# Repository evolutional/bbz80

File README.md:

# BBZ80

A breadboard Z80 computer loosely based on the Amstrad CPC 464 and targeting the RC2014 bus standard.

This is a work in progress project. Follow the story [on the blog](https://www.evolutional.co.uk/categories/bbz80/).

## Modules

- [Backplane](./docs/backplane/README.md)
- [Z80 CPU Board](./docs/z80-board/README.md)
- Clock board - TBD
- Serial IO board - TBD

## Acknowledgements

This project uses designs and standards based on [RC2014](https://rc2014.co.uk). It is not endorsed by or affiliated with RC2014 in any way whatsoever.

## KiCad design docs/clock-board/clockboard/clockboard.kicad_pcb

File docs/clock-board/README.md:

# Clock Board

The clock board takes a 16Mz oscillator and divides down to 8Mhz, 4Mhz, 2Mhz and 1Mhz clocks that can be mapped to the RC2014 `CLK` and/or `CLK2` lines.

Additionally, it has provision for an external clock `EXT` line that can be exposed to RC2014's `CLK` and/or `CLK2` lines.

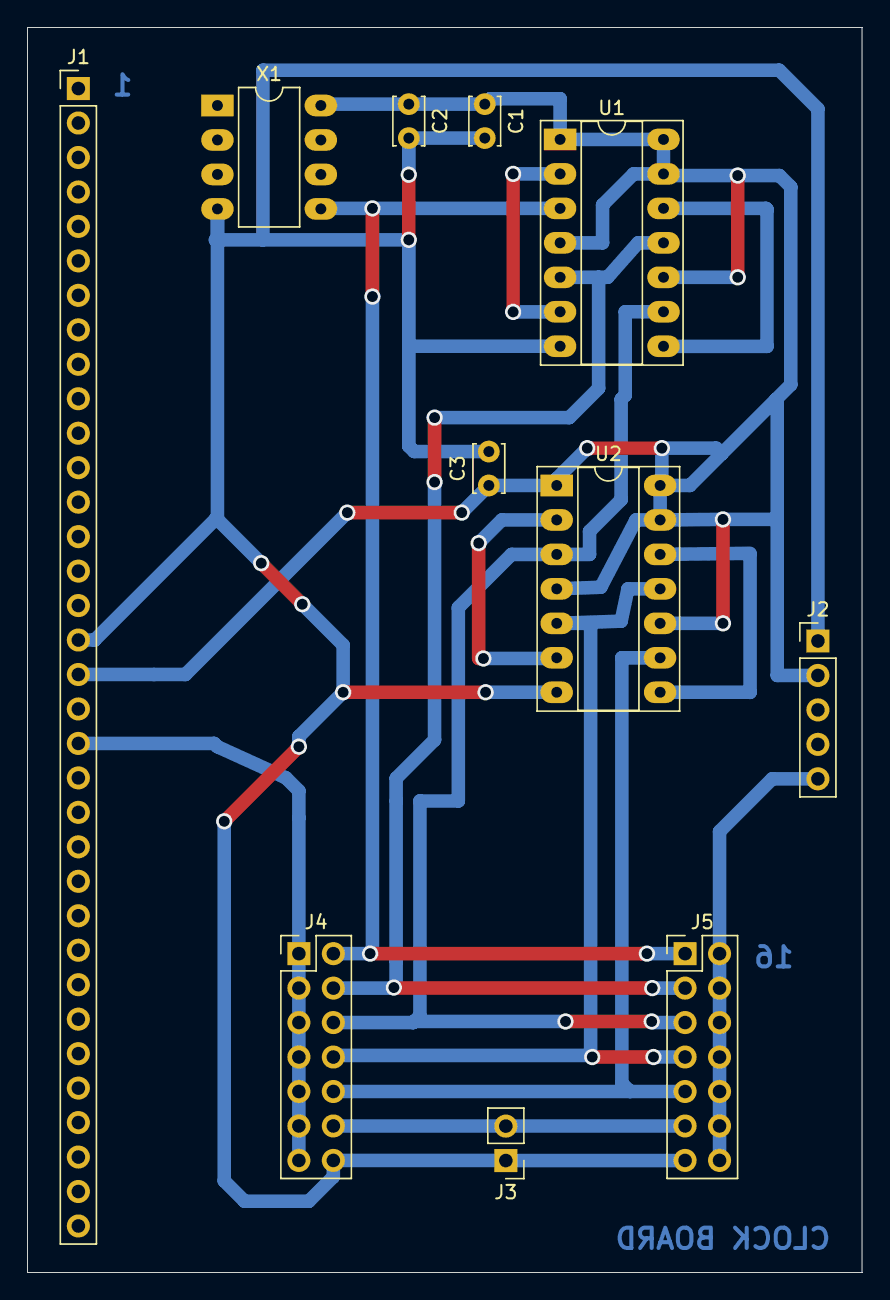
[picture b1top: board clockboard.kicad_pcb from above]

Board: 2 copper layers, 61.5 x 91.8 mm, 11 parts (0 on the bottom side), 14 nets.

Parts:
C1, C2, C3: C; C_Disc_D3.4mm_W2.1mm_P2.50mm
J1: Conn_01x34_Male; PinHeader_1x34_P2.54mm_Vertical
J2: Conn_01x05_Male; PinHeader_1x05_P2.54mm_Vertical
J3: Conn_01x02_Male; PinHeader_1x02_P2.54mm_Vertical
J4: Conn_02x07_Top_Bottom; PinHeader_2x07_P2.54mm_Vertical
J5: Conn_02x07_Counter_Clockwise; PinHeader_2x07_P2.54mm_Vertical
U1, U2: 74LS74; DIP-14_W7.62mm_Socket_LongPads
X1: CXO_DIP8; DIP-8_W7.62mm_LongPads

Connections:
CLK: J1.20, J4.1, J4.3, J4.5, J4.7, J4.9, J4.11, J4.13
CLK2: J2.5, J5.2, J5.4, J5.6, J5.8, J5.10, J5.12, J5.14
CLK_1: J4.10, J5.9, U2.9
CLK_2: J4.8, J5.7, U2.5, U2.11
CLK_4: J4.6, J5.5, U1.9, U2.3
CLK_8: J4.4, J5.3, U1.5, U1.11
CLK_16: J4.2, J5.1, U1.3, X1.5
CLK_EXT: J3.2, J4.12, J5.11
GND: C1.2, C2.2, C3.2, J1.17, J2.1, J3.1, J4.14, J5.13, U1.7, U2.7, X1.4
unnamed: U1.2, U1.6
unnamed: U1.8, U1.12
unnamed: U2.2, U2.6
unnamed: U2.8, U2.12
VCC: C1.1, C2.1, C3.1, J1.18, J2.2, U1.1, U1.4, U1.10, U1.13, U1.14, U2.1, U2.4, U2.10, U2.13, U2.14, X1.8

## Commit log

2022-01-02 hello, world
2022-01-02 fix image ref
2022-01-02 added backplane
2022-01-08 wip: clock board
